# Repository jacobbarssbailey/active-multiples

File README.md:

# Active Multiples
This project provides tested plans for a 4HP Eurorack-format synthesizer module, containing two banks of 1 -> 3 active buffers, taking any signal at the input and precisely replicating it on the three outputs.

## BOM 

Qty | Value            | Device                  | Package             | Parts                                                |
--- | ---------------- | ----------------------- | ------------------- | ---------------------------------------------------- |
3   | TL072            | Dual op amp             | TSSOP8              | ICxx                                                 |
6   | ~100nF           | Capacitor               | 0603                | DC1 – DC6                                            |
1   |                  | 5x2                     | 2.54mm Pin          | Power                                                |
8   |                  | Inline mono jack        | Thonkconn           | A, A1, A2, A3, B, B1, B2, B3                         |

## Notes

1. Solder the power connector before soldering signal jacks. There is very little space between the jacks to reach the top of the board after they are attached.
1. Input A (labeled on PCB) drives output A1, A2, A3; Input B drives output B1, B2, B3. Input A is normalled to Input B; if this behavior isn't desired, cut jumper trace labeled A->B.

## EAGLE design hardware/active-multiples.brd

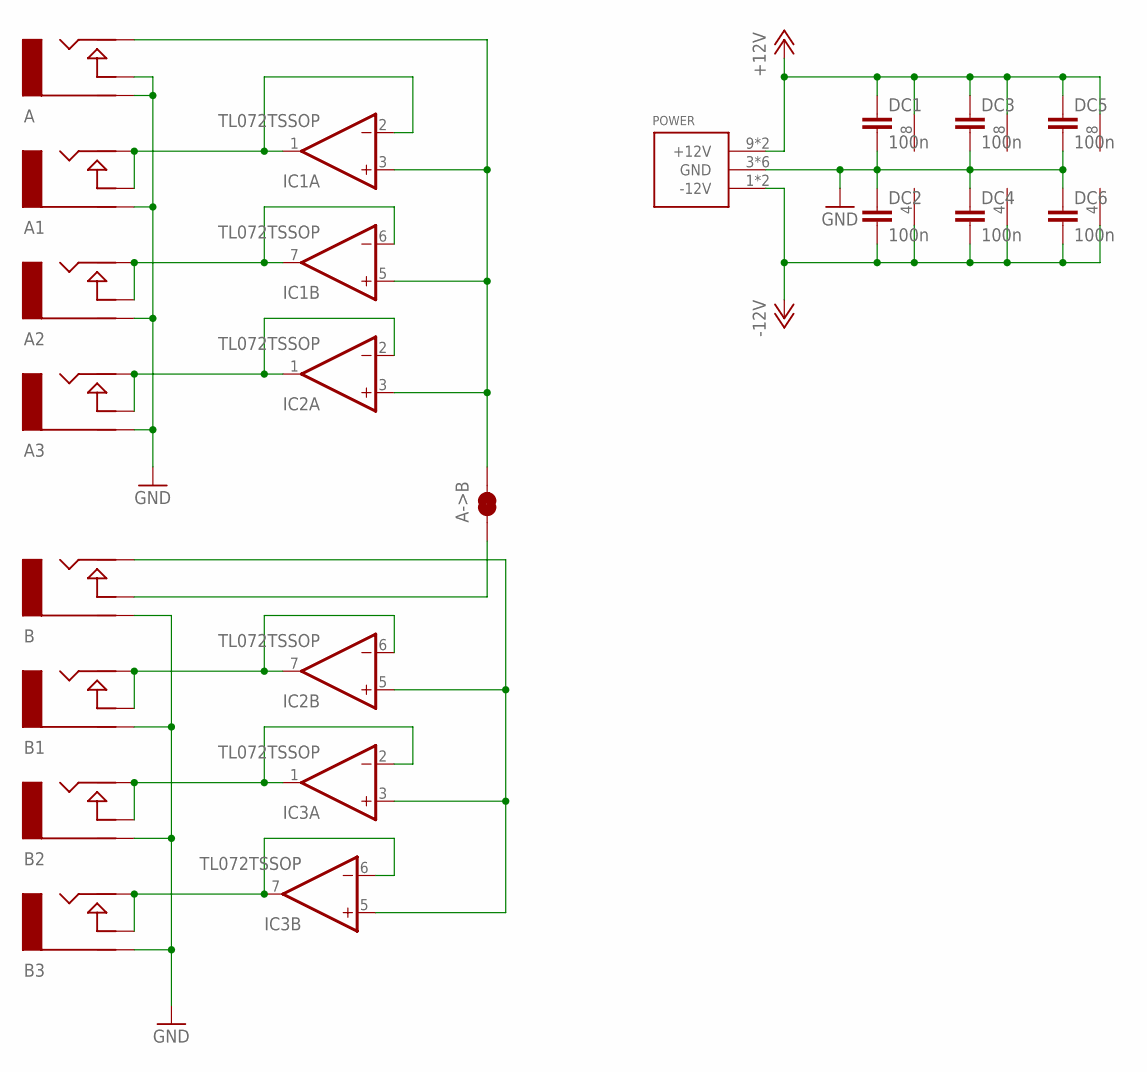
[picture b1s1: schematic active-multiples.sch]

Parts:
A, A1, A2, A3: AUDIO-JACKINLINE; ERTHENVAR-JACK-INLINE
A->B: JUMPER-PAD-2-NC_BY_TRACENO_SILK; PAD-JUMPER-2-NC_BY_TRACE_NO_SILK
B, B1, B2, B3: AUDIO-JACKINLINE; ERTHENVAR-JACK-INLINE
DC1, DC2, DC3, DC4, DC5, DC6: 100n; 0603-CAP
IC1, IC2, IC3: TL072TSSOP; TSSOP8
POWER: POWER_SIMPLE10; POWER_10

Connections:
+12V: DC1.1, DC3.1, DC5.1, IC1.8 (V+), IC2.8 (V+), IC3.8 (V+), POWER.9 (+12V), POWER.10 (+12V)
-12V: DC2.2, DC4.2, DC6.2, IC1.4 (V-), IC2.4 (V-), IC3.4 (V-), POWER.1 (-12V), POWER.2 (-12V)
GND: A.G (RING), A.N (NORM), A1.G (RING), A2.G (RING), A3.G (RING), B.G (RING), B1.G (RING), B2.G (RING), B3.G (RING), DC1.2, DC2.1, DC3.2, DC4.1, DC5.2, DC6.1, POWER.3 (GND), POWER.4 (GND), POWER.5 (GND), POWER.6 (GND), POWER.7 (GND), POWER.8 (GND)
unnamed: A1.N (NORM), A1.T (TIP), IC1.1 (OUT), IC1.2 (-IN)
unnamed: A->B.1, B.N (NORM)
unnamed: A3.N (NORM), A3.T (TIP), IC2.1 (OUT), IC2.2 (-IN)
unnamed: A2.N (NORM), A2.T (TIP), IC1.6 (-IN), IC1.7 (OUT)
unnamed: A.T (TIP), A->B.2, IC1.3 (+IN), IC1.5 (+IN), IC2.3 (+IN)
unnamed: B1.N (NORM), B1.T (TIP), IC2.6 (-IN), IC2.7 (OUT)
unnamed: B3.N (NORM), B3.T (TIP), IC3.6 (-IN), IC3.7 (OUT)
unnamed: B.T (TIP), IC2.5 (+IN), IC3.3 (+IN), IC3.5 (+IN)
unnamed: B2.N (NORM), B2.T (TIP), IC3.1 (OUT), IC3.2 (-IN)

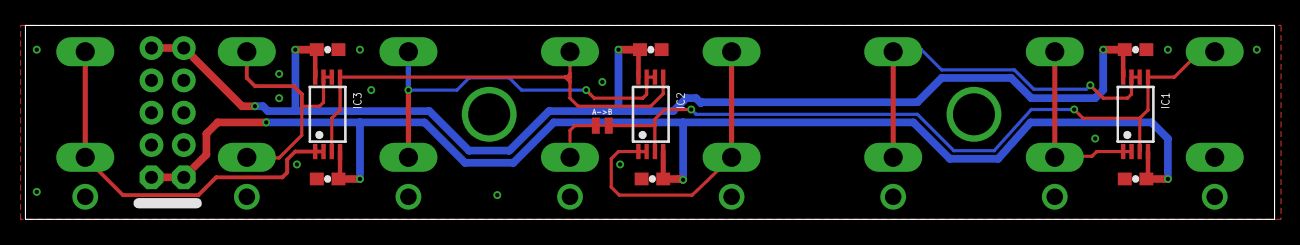
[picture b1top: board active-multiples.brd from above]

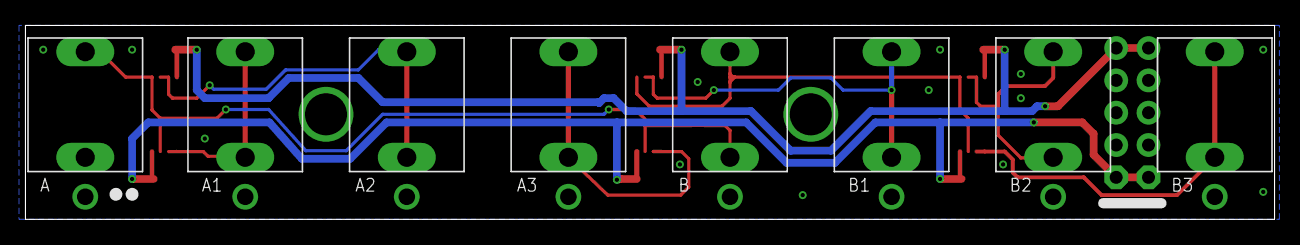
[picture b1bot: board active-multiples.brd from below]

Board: 2 copper layers, 98.2 x 15.2 mm, 19 parts (8 on the bottom side), 12 nets.

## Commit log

2019-05-19 init
2019-05-19 fix intro
2019-05-20 bom, desc, pcbs
2019-05-20 read me
2019-05-20 photos
2019-05-20 fix photo reference
2019-05-20 bom formatting

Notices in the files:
parts and their libraries:
SparkFun-Passives: Licensing: Creative Commons ShareAlike 4.0 International - https://creativecommons.org/licenses/by-sa/4.0
